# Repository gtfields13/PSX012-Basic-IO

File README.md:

# PSX013 Basic IO
Basic Unified IO Board

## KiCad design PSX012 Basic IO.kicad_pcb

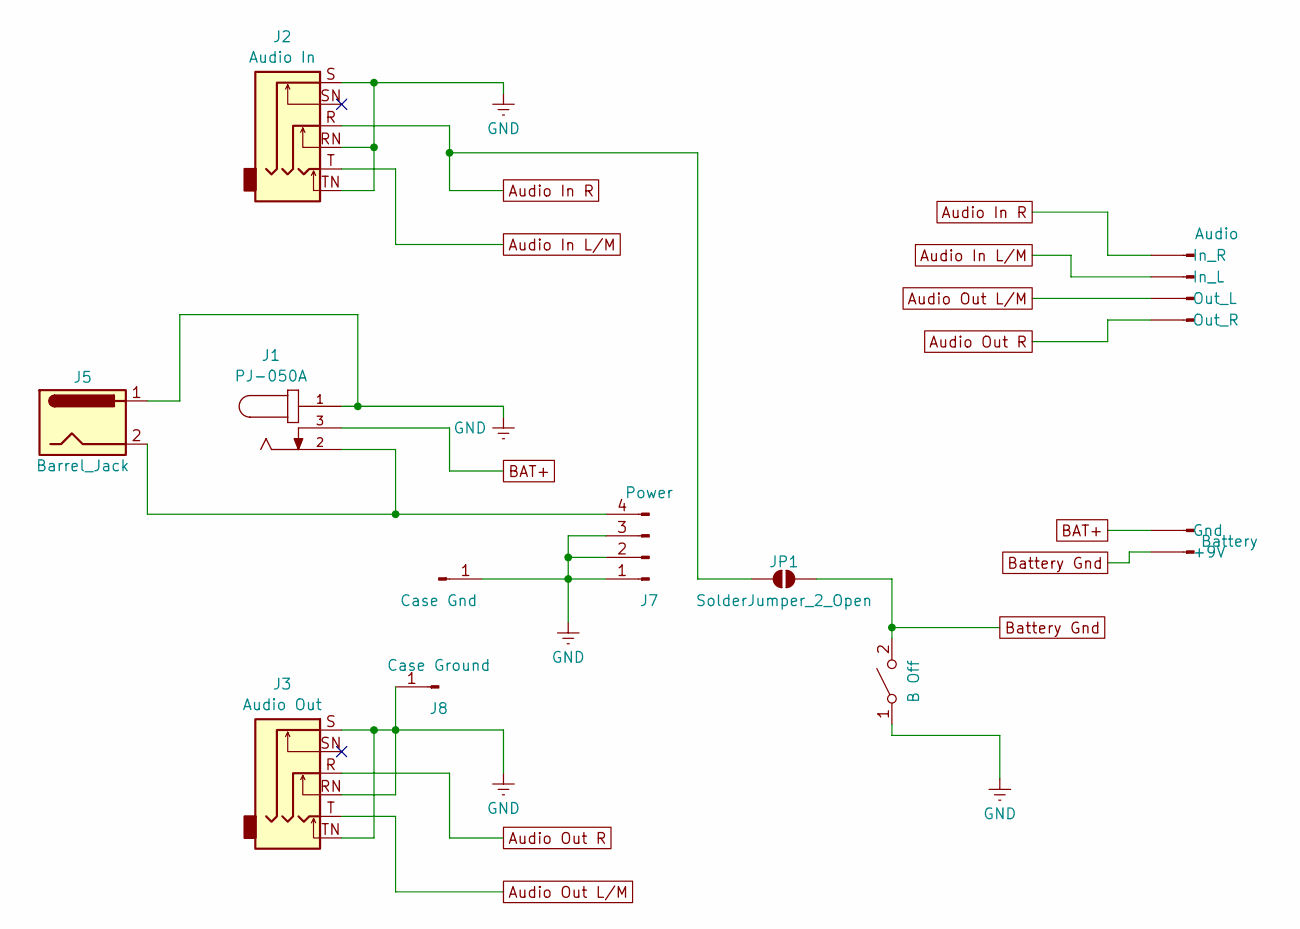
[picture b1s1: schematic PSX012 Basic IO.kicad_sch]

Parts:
J1: PJ-050A; PARTREV 1.02
J2: Audio In; Jack_6.35mm_Neutrik_NMJ6HF-S_Horizontal
J3: Audio Out; Jack_6.35mm_Neutrik_NMJ6HF-S_Horizontal
J4: Audio; JST_PH_S4B-PH-K_1x04_P2.00mm_Horizontal
J5: Barrel_Jack; JST_PH_S2B-PH-K_1x02_P2.00mm_Horizontal
J6: Battery; JST_PH_S2B-PH-K_1x02_P2.00mm_Horizontal
J7: Power; JST_PH_S4B-PH-K_1x04_P2.00mm_Horizontal
J8: Case Ground; Grounding Washer_Cliff
J9: Case Gnd; TestPoint_THTPad_D2.0mm_Drill1.0mm
JP1: SolderJumper_2_Open; SolderJumper-2_P1.3mm_Open_RoundedPad1.0x1.5mm
SW1: B Off; JST_PH_S2B-PH-K_1x02_P2.00mm_Horizontal

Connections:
Audio In L/M: J2.T, J4.3 (In_L)
Audio In R: J2.R, J4.4 (In_R), JP1.1 (A)
Audio Out L/M: J3.T, J4.2 (Out_L)
Audio Out R: J3.R, J4.1 (Out_R)
BAT+: J1.3, J6.2 (Gnd)
Battery Gnd: J6.1 (+9V), JP1.2 (B), SW1.2 (B)
GND: J1.1, J2.RN, J2.S, J2.TN, J3.RN, J3.S, J3.TN, J5.1, J7.1, J7.2, J7.3, J8.1 (Ground), J9.1, SW1.1 (A)
unnamed: J1.2, J5.2, J7.4

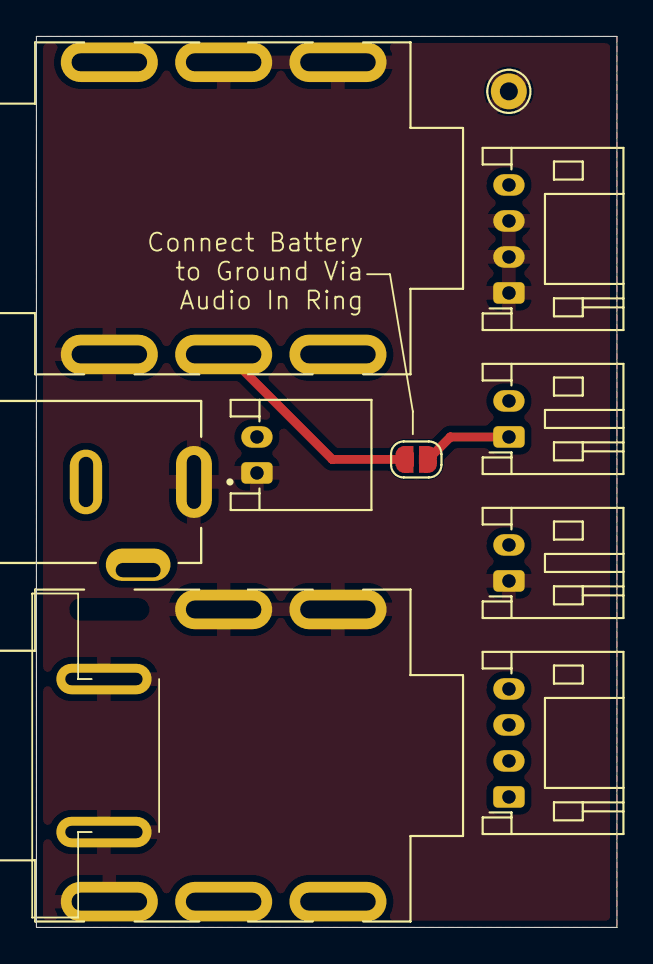
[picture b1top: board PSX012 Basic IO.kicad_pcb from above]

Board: 4 copper layers, 32.2 x 49.5 mm, 11 parts (1 on the bottom side), 8 nets.
